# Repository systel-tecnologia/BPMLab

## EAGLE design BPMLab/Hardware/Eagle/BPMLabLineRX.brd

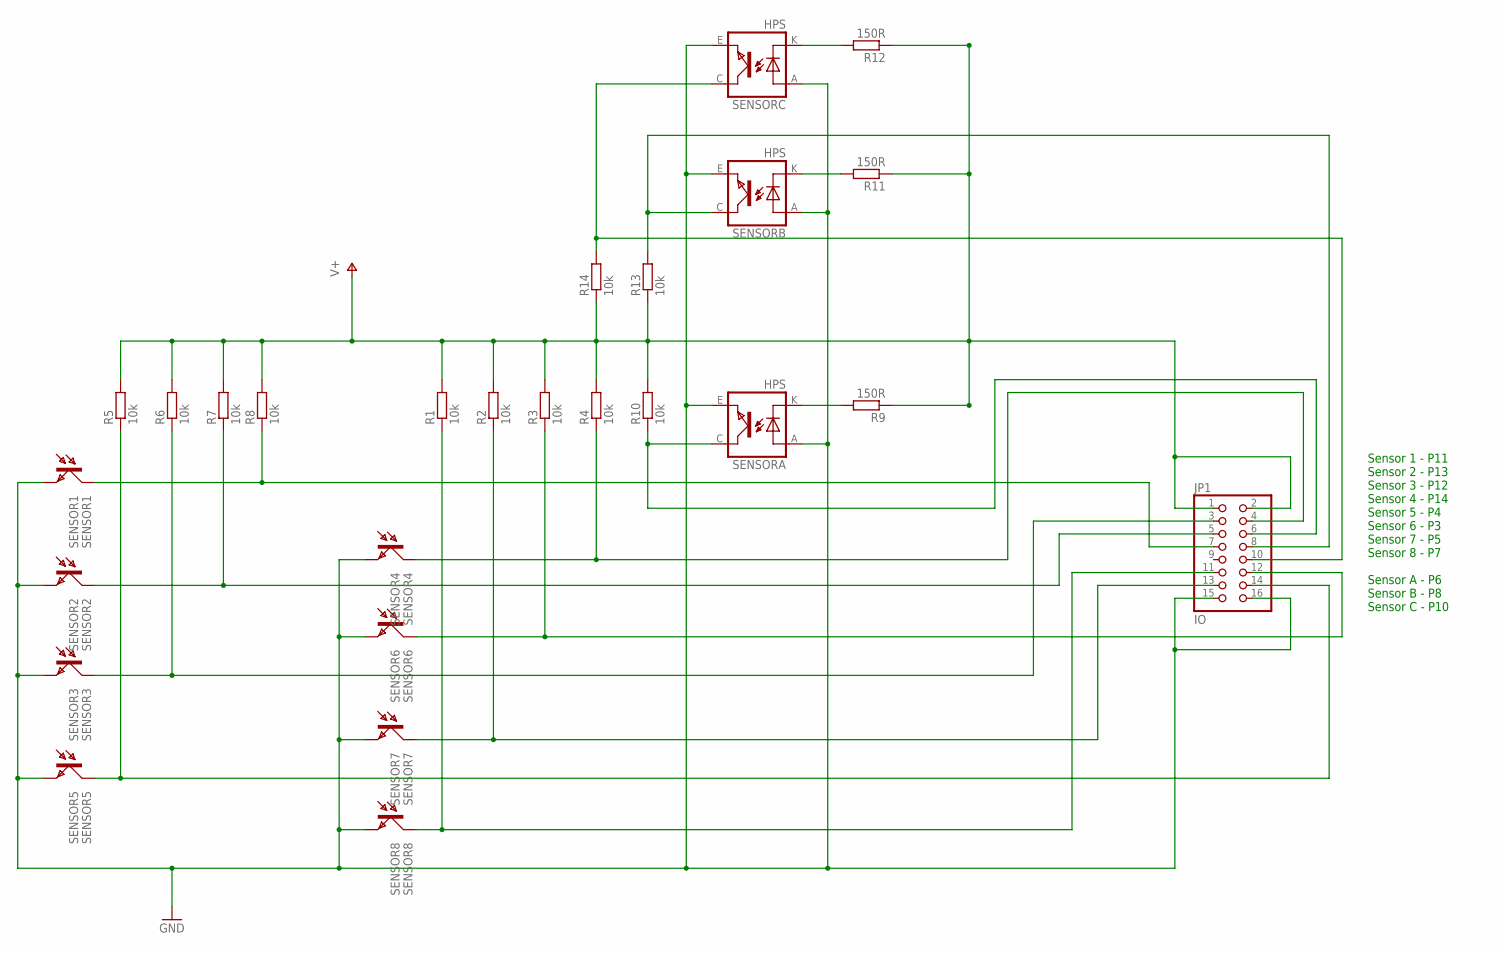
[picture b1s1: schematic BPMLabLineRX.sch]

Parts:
JP1: IO; 2X08
R1, R2, R3, R4, R5, R6, R7, R8, R10, R13, R14: 10k; M0805
R9, R11, R12: 150R; M0805
SENSOR1: SENSOR1; BPX81
SENSOR2: SENSOR2; BPX81
SENSOR3: SENSOR3; BPX81
SENSOR4: SENSOR4; BPX81
SENSOR5: SENSOR5; BPX81
SENSOR6: SENSOR6; BPX81
SENSOR7: SENSOR7; BPX81
SENSOR8: SENSOR8; BPX81
SENSORA: HPS; TCRT5000
SENSORB: HPS; TCRT5000
SENSORC: HPS; TCRT5000

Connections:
GND: JP1.15, JP1.16, SENSOR1.E, SENSOR2.E, SENSOR3.E, SENSOR4.E, SENSOR5.E, SENSOR6.E, SENSOR7.E, SENSOR8.E, SENSORA.A (ANODE), SENSORA.E (EMITTER), SENSORB.A (ANODE), SENSORB.E (EMITTER), SENSORC.A (ANODE), SENSORC.E (EMITTER)
unnamed: JP1.4, R4.1, SENSOR4.C
unnamed: JP1.12, R3.1, SENSOR6.C
unnamed: JP1.13, R2.1, SENSOR7.C
unnamed: JP1.11, R1.1, SENSOR8.C
unnamed: JP1.7, R8.1, SENSOR1.C
unnamed: JP1.5, R7.1, SENSOR2.C
unnamed: JP1.3, R6.1, SENSOR3.C
unnamed: JP1.14, R5.1, SENSOR5.C
unnamed: JP1.6, R10.1, SENSORA.C (COLLECTOR)
unnamed: R9.2, SENSORA.K (CATHODE)
unnamed: R12.2, SENSORC.K (CATHODE)
unnamed: R11.2, SENSORB.K (CATHODE)
unnamed: JP1.8, R13.2, SENSORB.C (COLLECTOR)
unnamed: JP1.10, R14.2, SENSORC.C (COLLECTOR)
V+: JP1.1, JP1.2, R1.2, R2.2, R3.2, R4.2, R5.2, R6.2, R7.2, R8.2, R9.1, R10.2, R11.1, R12.1, R13.1, R14.1

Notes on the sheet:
Sensor 1 - P11 Sensor 2 - P13 Sensor 3 - P12 Sensor 4 - P14 Sensor 5 - P4 Sensor 6 - P3 Sensor 7 - P5 Sensor 8 - P7 Sensor A - P6 Sensor B - P8 Sensor C - P10

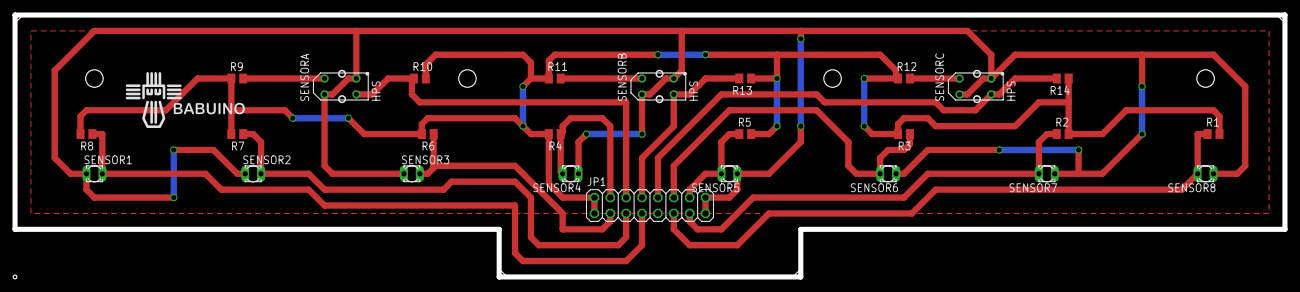
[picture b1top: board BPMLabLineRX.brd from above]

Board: 2 copper layers, 203.2 x 41.9 mm, 26 parts (0 on the bottom side), 16 nets.

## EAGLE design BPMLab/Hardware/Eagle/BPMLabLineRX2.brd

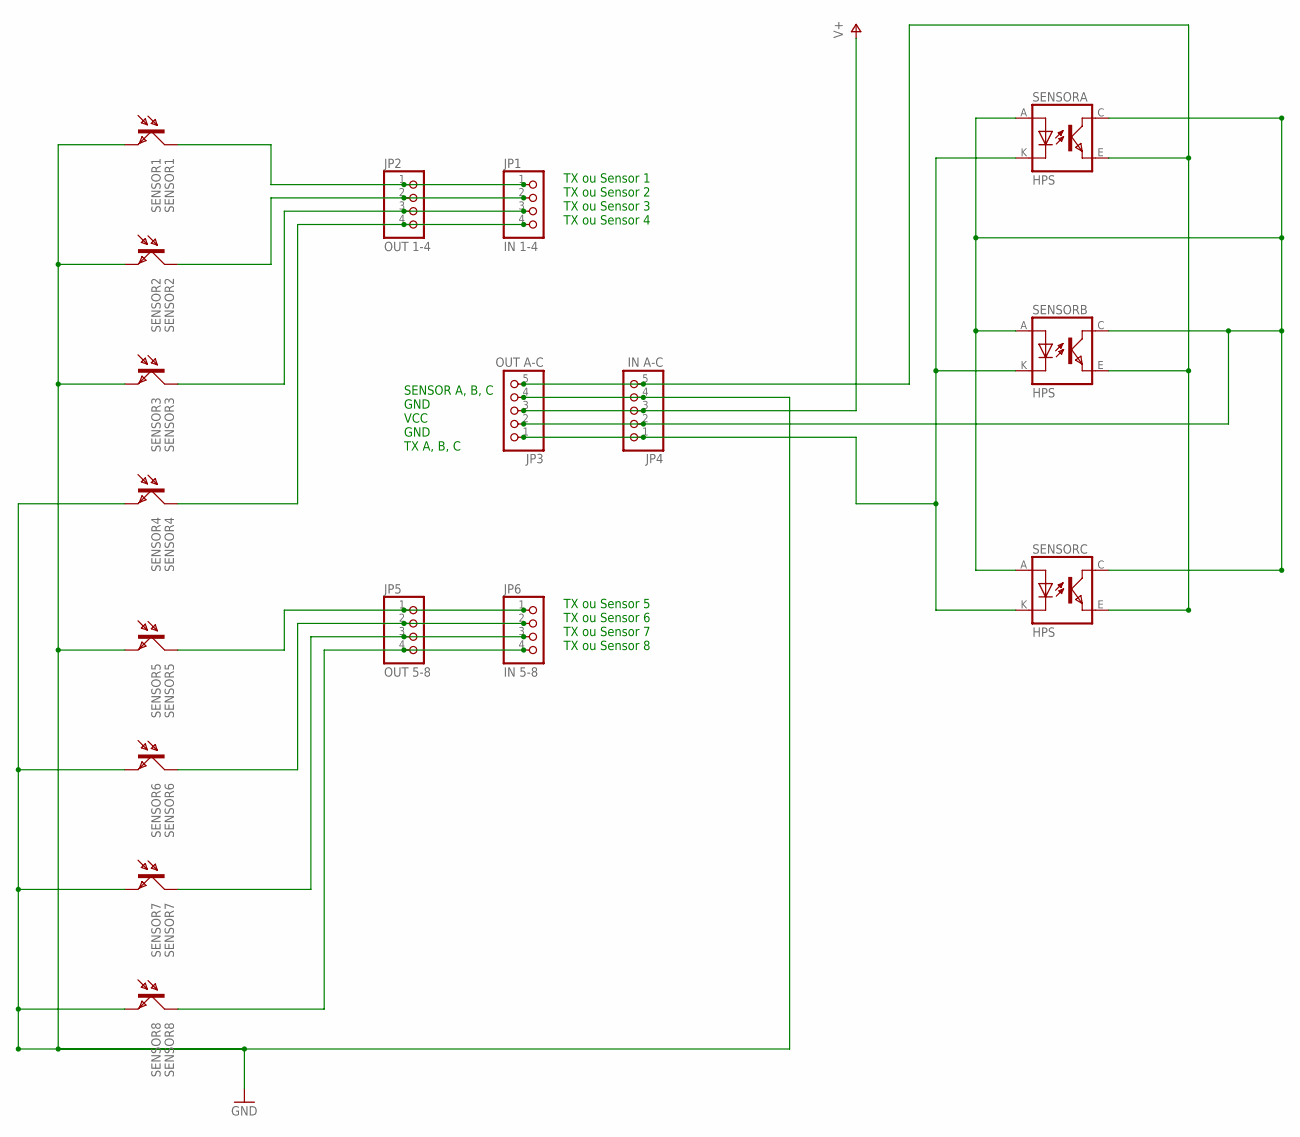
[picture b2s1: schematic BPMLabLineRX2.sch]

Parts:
JP1: IN 1-4; 1X04
JP2: OUT 1-4; 1X04
JP3: OUT A-C; 1X05
JP4: IN A-C; 1X05
JP5: OUT 5-8; 1X04
JP6: IN 5-8; 1X04
SENSOR1: SENSOR1; BPX81
SENSOR2: SENSOR2; BPX81
SENSOR3: SENSOR3; BPX81
SENSOR4: SENSOR4; BPX81
SENSOR5: SENSOR5; BPX81
SENSOR6: SENSOR6; BPX81
SENSOR7: SENSOR7; BPX81
SENSOR8: SENSOR8; BPX81
SENSORA: HPS; TCRT5000
SENSORB: HPS; TCRT5000
SENSORC: HPS; TCRT5000

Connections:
GND: JP3.4, JP4.4, SENSOR1.E, SENSOR2.E, SENSOR3.E, SENSOR4.E, SENSOR5.E, SENSOR6.E, SENSOR7.E, SENSOR8.E
unnamed: JP1.4, JP2.4, SENSOR4.C
unnamed: JP5.2, JP6.2, SENSOR6.C
unnamed: JP5.3, JP6.3, SENSOR7.C
unnamed: JP5.4, JP6.4, SENSOR8.C
unnamed: JP1.1, JP2.1, SENSOR1.C
unnamed: JP1.2, JP2.2, SENSOR2.C
unnamed: JP1.3, JP2.3, SENSOR3.C
unnamed: JP5.1, JP6.1, SENSOR5.C
unnamed: JP3.5, JP4.5, SENSORA.E (EMITTER), SENSORB.E (EMITTER), SENSORC.E (EMITTER)
unnamed: JP3.1, JP4.1, SENSORA.K (CATHODE), SENSORB.K (CATHODE), SENSORC.K (CATHODE)
unnamed: JP3.2, JP4.2, SENSORA.A (ANODE), SENSORA.C (COLLECTOR), SENSORB.A (ANODE), SENSORB.C (COLLECTOR), SENSORC.A (ANODE), SENSORC.C (COLLECTOR)
V+: JP3.3, JP4.3

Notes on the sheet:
TX ou Sensor 1 TX ou Sensor 2 TX ou Sensor 3 TX ou Sensor 4
TX ou Sensor 5 TX ou Sensor 6 TX ou Sensor 7 TX ou Sensor 8
SENSOR A, B, C GND VCC GND TX A, B, C

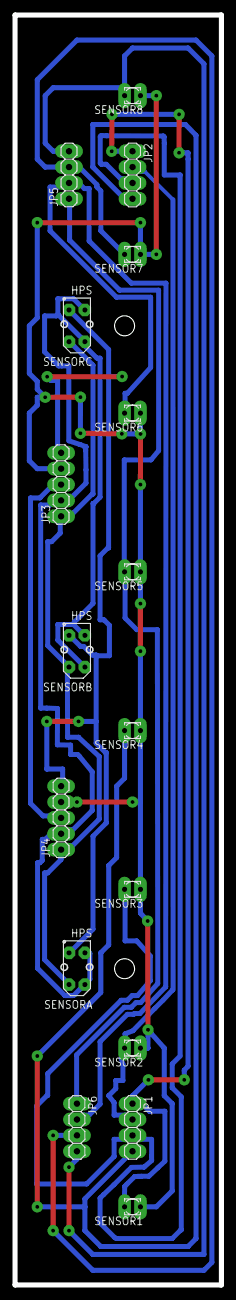
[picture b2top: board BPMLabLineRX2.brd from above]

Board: 2 copper layers, 33.0 x 203.2 mm, 17 parts (0 on the bottom side), 13 nets.

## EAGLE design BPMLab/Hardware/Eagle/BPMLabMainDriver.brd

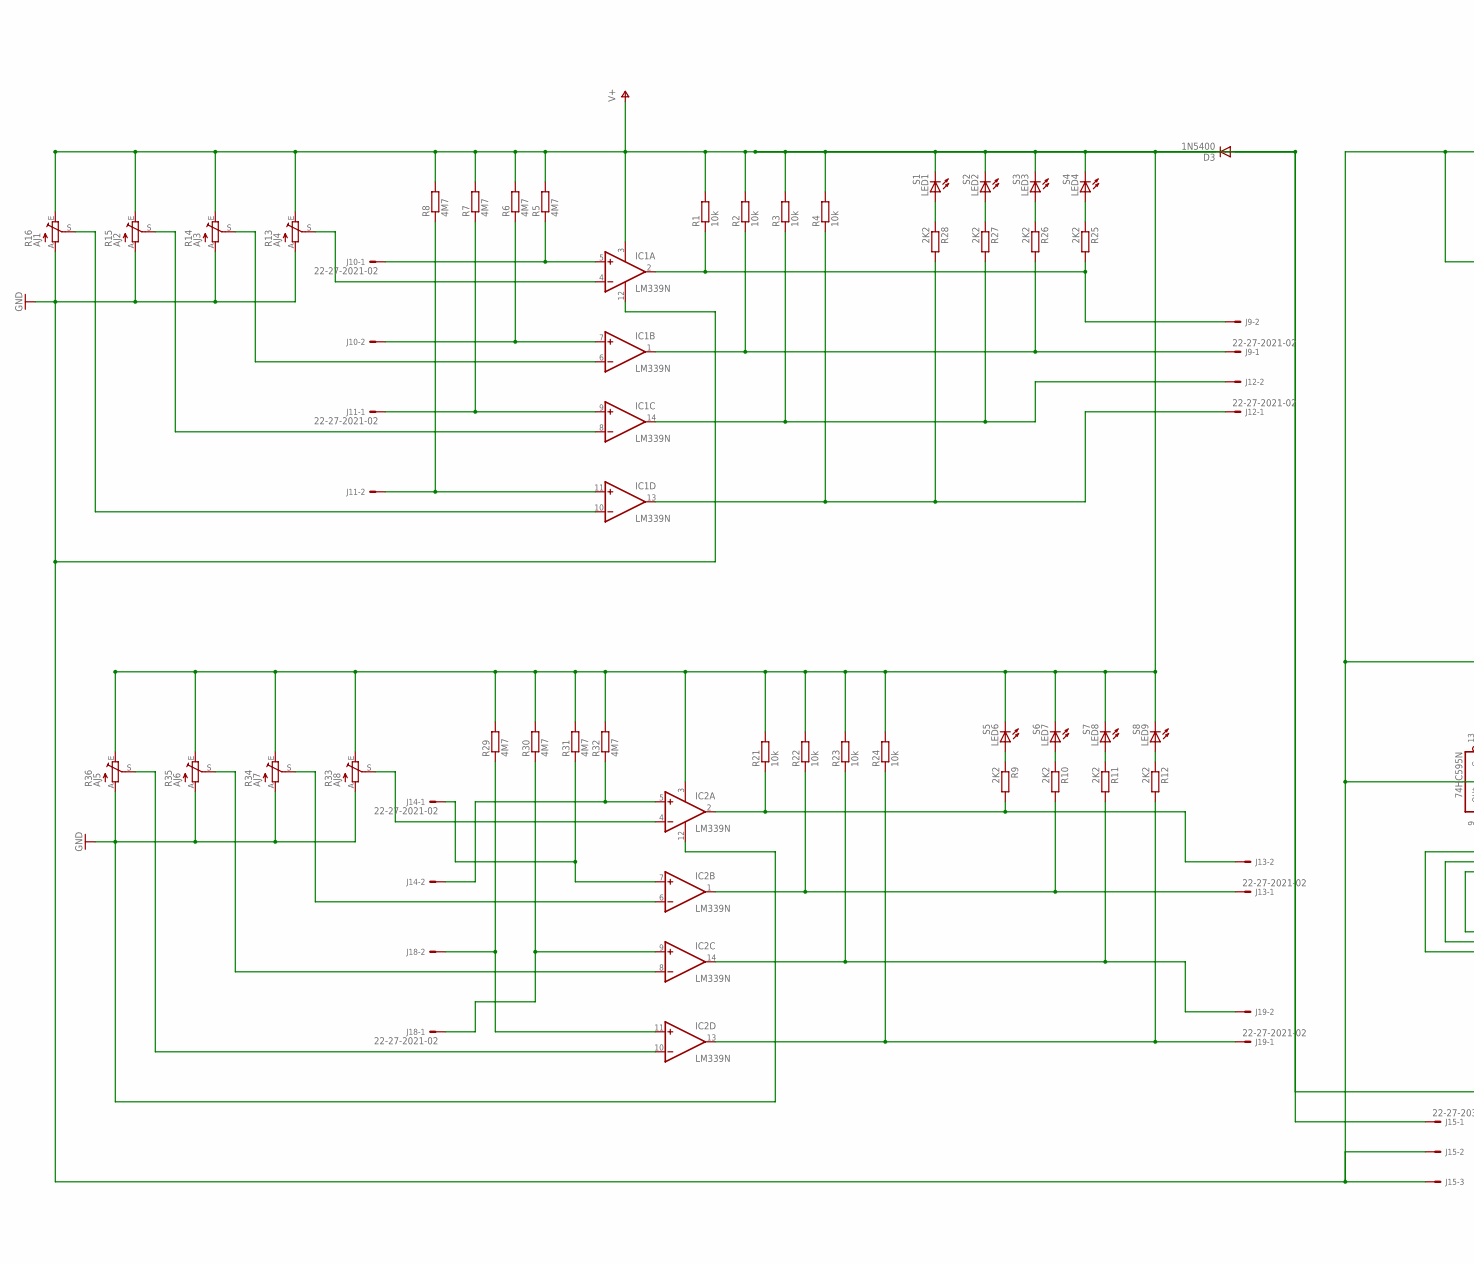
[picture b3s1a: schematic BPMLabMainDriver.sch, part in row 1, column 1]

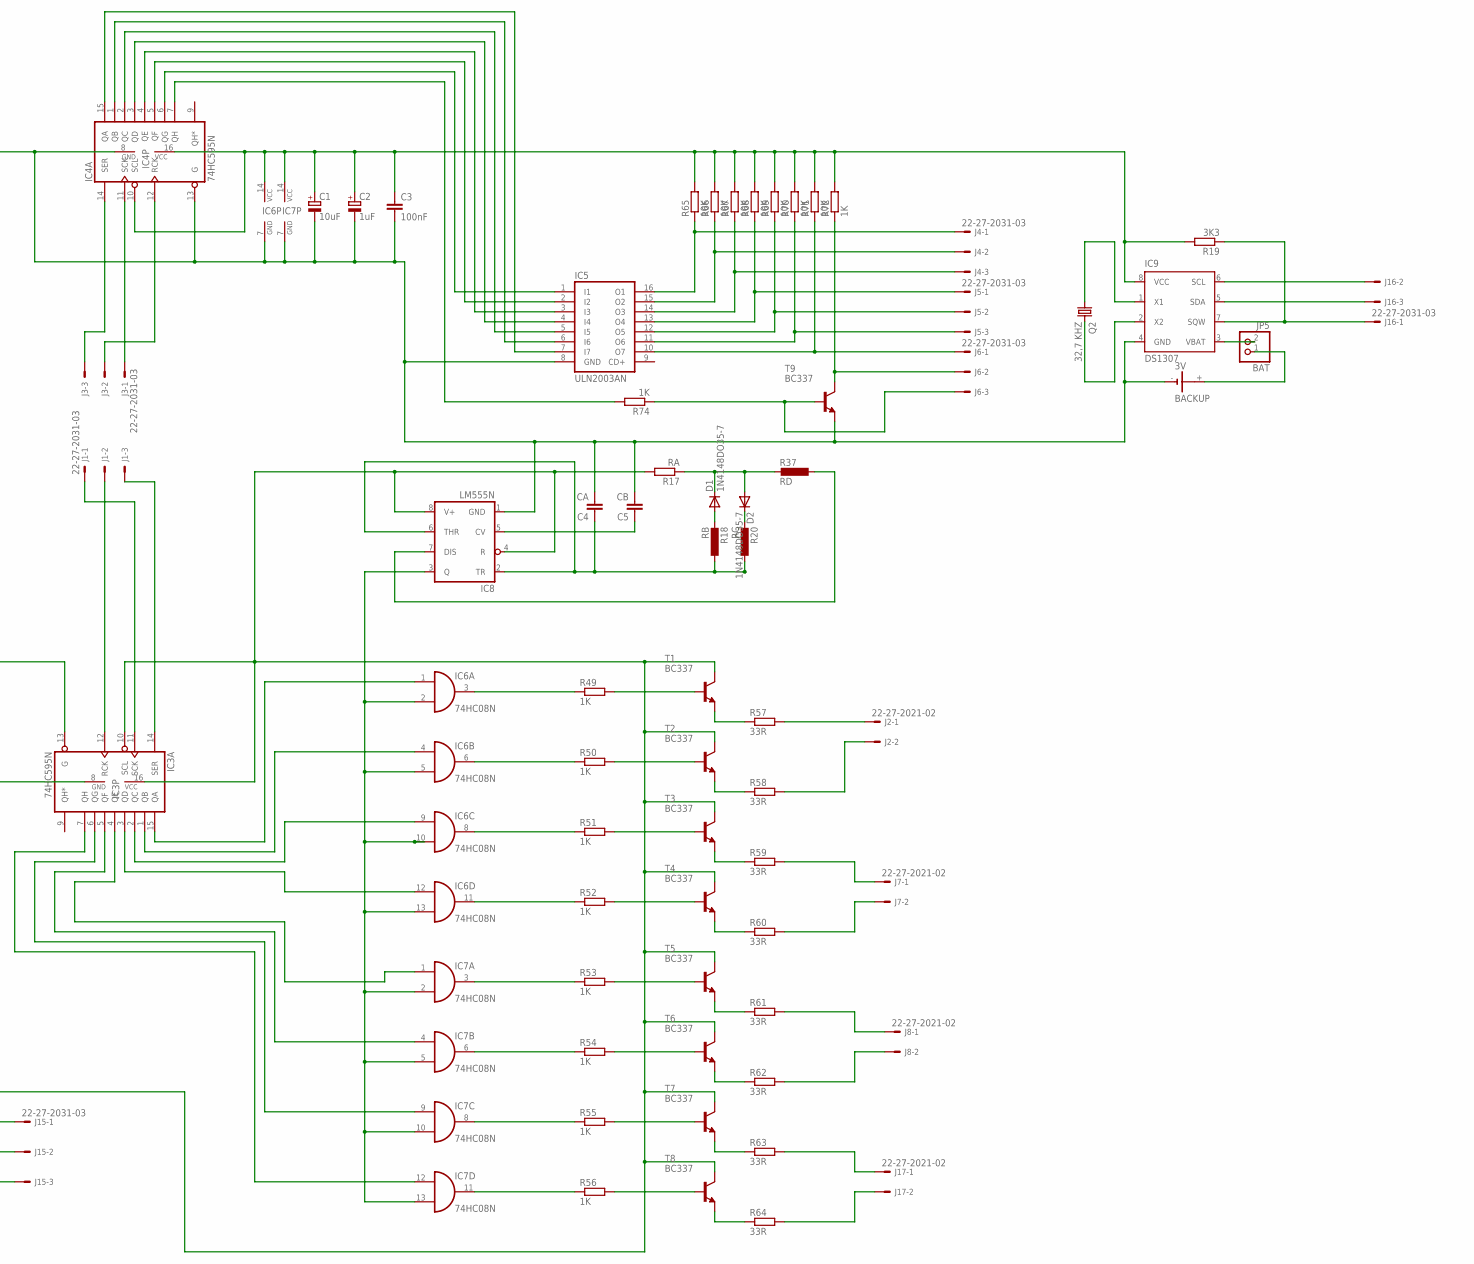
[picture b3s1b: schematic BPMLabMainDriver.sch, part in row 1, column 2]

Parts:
3V: BACKUP; CR2032V
BAT: JP5; 1X02
C1: 10uF; E2,5-6
C2: 1uF; E2,5-6
C3: 100nF; C050-024X044
C4: CA; C050-025X075
C5: CB; C050-024X044
D1, D2: 1N4148DO35-7; DO35-7
D3: 1N5400; DO201-15
IC1, IC2: LM339N; DIL14
IC3, IC4: 74HC595N; DIL16
IC5: ULN2003AN; DIL16
IC6, IC7: 74HC08N; DIL14
IC8: LM555N; DIL08
IC9: DS1307; DIL08
J1, J3, J4, J5, J6, J15, J16: 22-27-2031-03; 6410-03
J2, J7, J8, J9, J10, J11, J12, J13, J14, J17, J18, J19: 22-27-2021-02; 6410-02
LED1: S1; LED5MM
LED2: S2; LED5MM
LED3: S3; LED5MM
LED4: S4; LED5MM
LED6: S5; LED5MM
LED7: S6; LED5MM
LED8: S7; LED5MM
LED9: S8; LED5MM
Q2: 32,7 KHZ; TC38H
R1, R2, R3, R4, R21, R22, R23, R24: 10k; 0207/7
R5, R6, R7, R8, R30, R31, R32: 4M7; 0207/10
R9, R10, R11, R12, R25, R26, R27, R28: 2K2; 0207/7
R13: AJ4; RS3
R14: AJ3; RS3
R15: AJ2; RS3
R16: AJ1; RS3
R17: RA; 0207/10
R18: RB; 0207/12
R19: 3K3; 0207/10
R20: RC; 0207/12
R29: 4M7; 0207/7
R33: AJ8; RS3
R34: AJ7; RS3
R35: AJ6; RS3
R36: AJ5; RS3
R37: RD; 0207/12
R49, R50, R51, R52, R53, R54, R55, R72, R74: 1K; 0207/10
R56: 1K; 0207/12
R57, R58, R59, R60, R61, R62, R63, R64: 33R; 0207/10
R65, R66, R67, R68, R69, R70, R71: 10K; 0207/10
T1, T2, T3, T4, T5, T6, T7, T8, T9: BC337; TO92

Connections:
GND: 3V.-, C1.-, C2.-, C3.2, C4.2, C5.2, IC1.12 (GND), IC2.12 (GND), IC3.8 (GND), IC3.13 (G), IC4.8 (GND), IC4.13 (G), IC5.8 (GND), IC6.7 (GND), IC7.7 (GND), IC8.1 (GND), IC9.4 (GND), J15.2, J15.3, R13.A, R14.A, R15.A, R16.A, R33.A, R34.A, R35.A, R36.A, T9.1 (E)
unnamed: IC1.2 (OUT), J9.2, R1.1, R25.2
unnamed: IC1.1 (OUT), J9.1, R2.1, R26.2
unnamed: IC1.14 (OUT), J12.2, R3.1, R27.2
unnamed: IC1.13 (OUT), J12.1, R4.1, R28.2
unnamed: IC1.5 (+IN), J10.1, R5.1
unnamed: IC1.7 (+IN), J10.2, R6.1
unnamed: IC1.9 (+IN), J11.1, R7.1
unnamed: IC1.11 (+IN), J11.2, R8.1
unnamed: IC5.16 (O1), J4.1, R65.1
unnamed: IC1.10 (-IN), R16.S
unnamed: IC1.8 (-IN), R15.S
unnamed: IC1.4 (-IN), R13.S
unnamed: IC1.6 (-IN), R14.S
unnamed: IC6.2 (I1), IC6.5 (I1), IC6.10 (I1), IC6.13 (I1), IC7.2 (I1), IC7.5 (I1), IC7.10 (I1), IC7.13 (I1), IC8.3 (Q)
unnamed: D1.A, R18.2
unnamed: D2.C, R20.2
unnamed: LED6.A, R9.1
unnamed: LED7.A, R10.1
unnamed: LED8.A, R11.1
unnamed: LED9.A, R12.1
unnamed: IC3.1 (QB), IC6.4 (I0)
unnamed: D1.C, D2.A, R17.1, R37.2
unnamed: C5.1, IC8.5 (CV)
unnamed: IC8.7 (DIS), R37.1
unnamed: IC2.2 (OUT), J13.2, R9.2, R21.1
unnamed: 3V.+, BAT.1
unnamed: IC2.1 (OUT), J13.1, R10.2, R22.1
unnamed: LED1.A, R28.1
unnamed: LED2.A, R27.1
unnamed: LED3.A, R26.1
unnamed: LED4.A, R25.1
unnamed: IC2.14 (OUT), J19.2, R11.2, R23.1
unnamed: IC2.13 (OUT), J19.1, R12.2, R24.1
unnamed: IC2.10 (-IN), R36.S
unnamed: IC2.8 (-IN), R35.S
unnamed: IC2.4 (-IN), R33.S
unnamed: IC2.6 (-IN), R34.S
unnamed: IC2.5 (+IN), J14.2, R32.1
unnamed: IC2.7 (+IN), J14.1, R31.1
unnamed: IC2.9 (+IN), J18.1, R30.1
unnamed: IC2.11 (+IN), J18.2, R29.1
unnamed: IC9.6 (SCL), J16.2
unnamed: IC9.5 (SDA), J16.3
unnamed: IC3.2 (QC), IC6.9 (I0)
unnamed: IC3.3 (QD), IC6.12 (I0)
unnamed: IC3.4 (QE), IC7.1 (I0)
unnamed: IC3.5 (QF), IC7.4 (I0)
unnamed: IC3.6 (QG), IC7.9 (I0)
unnamed: IC3.7 (QH), IC7.12 (I0)
unnamed: IC6.3 (O), R49.1
unnamed: IC6.6 (O), R50.1
unnamed: IC6.8 (O), R51.1
unnamed: IC3.15 (QA), IC6.1 (I0)
unnamed: IC6.11 (O), R52.1
unnamed: IC7.3 (O), R53.1
unnamed: IC7.6 (O), R54.1
unnamed: IC7.8 (O), R55.1
unnamed: IC7.11 (O), R56.1
unnamed: C4.1, IC8.2 (TR), IC8.6 (THR), R18.1, R20.1
unnamed: J17.2, R64.2
unnamed: R49.2, T1.2 (B)
unnamed: R50.2, T2.2 (B)
unnamed: R51.2, T3.2 (B)
unnamed: R52.2, T4.2 (B)
unnamed: R53.2, T5.2 (B)
unnamed: R54.2, T6.2 (B)
unnamed: R56.2, T8.2 (B)
unnamed: R55.2, T7.2 (B)
unnamed: R57.1, T1.1 (E)
unnamed: R58.1, T2.1 (E)
unnamed: R59.1, T3.1 (E)
unnamed: R60.1, T4.1 (E)
unnamed: R61.1, T5.1 (E)
unnamed: R62.1, T6.1 (E)
unnamed: R63.1, T7.1 (E)
unnamed: R64.1, T8.1 (E)
unnamed: J8.1, R61.2
unnamed: IC3.11 (SCK), J1.1
unnamed: IC3.12 (RCK), J1.2
unnamed: IC3.14 (SER), J1.3
unnamed: J8.2, R62.2
unnamed: J17.1, R63.2
unnamed: J7.2, R60.2
unnamed: J7.1, R59.2
unnamed: J2.2, R58.2
unnamed: J2.1, R57.2
unnamed: IC4.15 (QA), IC5.7 (I7)
unnamed: IC4.1 (QB), IC5.6 (I6)
unnamed: IC4.2 (QC), IC5.5 (I5)
unnamed: IC4.3 (QD), IC5.4 (I4)
unnamed: IC4.4 (QE), IC5.3 (I3)
unnamed: IC4.5 (QF), IC5.2 (I2)
unnamed: IC4.6 (QG), IC5.1 (I1)
unnamed: IC5.15 (O2), J4.2, R66.1
unnamed: IC5.14 (O3), J4.3, R67.1
unnamed: IC4.11 (SCK), J3.1
unnamed: IC4.12 (RCK), J3.2
unnamed: IC4.14 (SER), J3.3
unnamed: IC5.13 (O4), J5.1, R68.1
unnamed: D3.A, J15.1
unnamed: IC5.12 (O5), J5.2, R69.1
unnamed: IC5.11 (O6), J5.3, R70.1
unnamed: IC5.10 (O7), J6.1, R71.1
unnamed: J6.2, R72.1, T9.3 (C)
unnamed: J6.3, R74.1, T9.2 (B)
unnamed: IC4.7 (QH), R74.2
unnamed: IC9.7 (SQW), J16.1, R19.1
unnamed: IC9.1 (X1), Q2.1
unnamed: IC9.2 (X2), Q2.2
unnamed: BAT.2, IC9.3 (VBAT)
VCC: C1.+, C2.+, C3.1, D3.C, IC1.3 (V+), IC2.3 (V+), IC3.10 (SCL), IC3.16 (VCC), IC4.10 (SCL), IC4.16 (VCC), IC6.14 (VCC), IC7.14 (VCC), IC8.4 (R), IC8.8 (V+), IC9.8 (VCC), LED1.K (C), LED2.K (C), LED3.K (C), LED4.K (C), LED6.K (C), LED7.K (C), LED8.K (C), LED9.K (C), R1.2, R2.2, R3.2, R4.2, R5.2, R6.2, R7.2, R8.2, R13.E, R14.E, R15.E, R16.E, R17.2, R19.2, R21.2, R22.2, R23.2, R24.2, R29.2, R30.2, R31.2, R32.2, R33.E, R34.E, R35.E, R36.E, R65.2, R66.2, R67.2, R68.2, R69.2, R70.2, R71.2, R72.2, T1.3 (C), T2.3 (C), T3.3 (C), T4.3 (C), T5.3 (C), T6.3 (C), T7.3 (C), T8.3 (C)

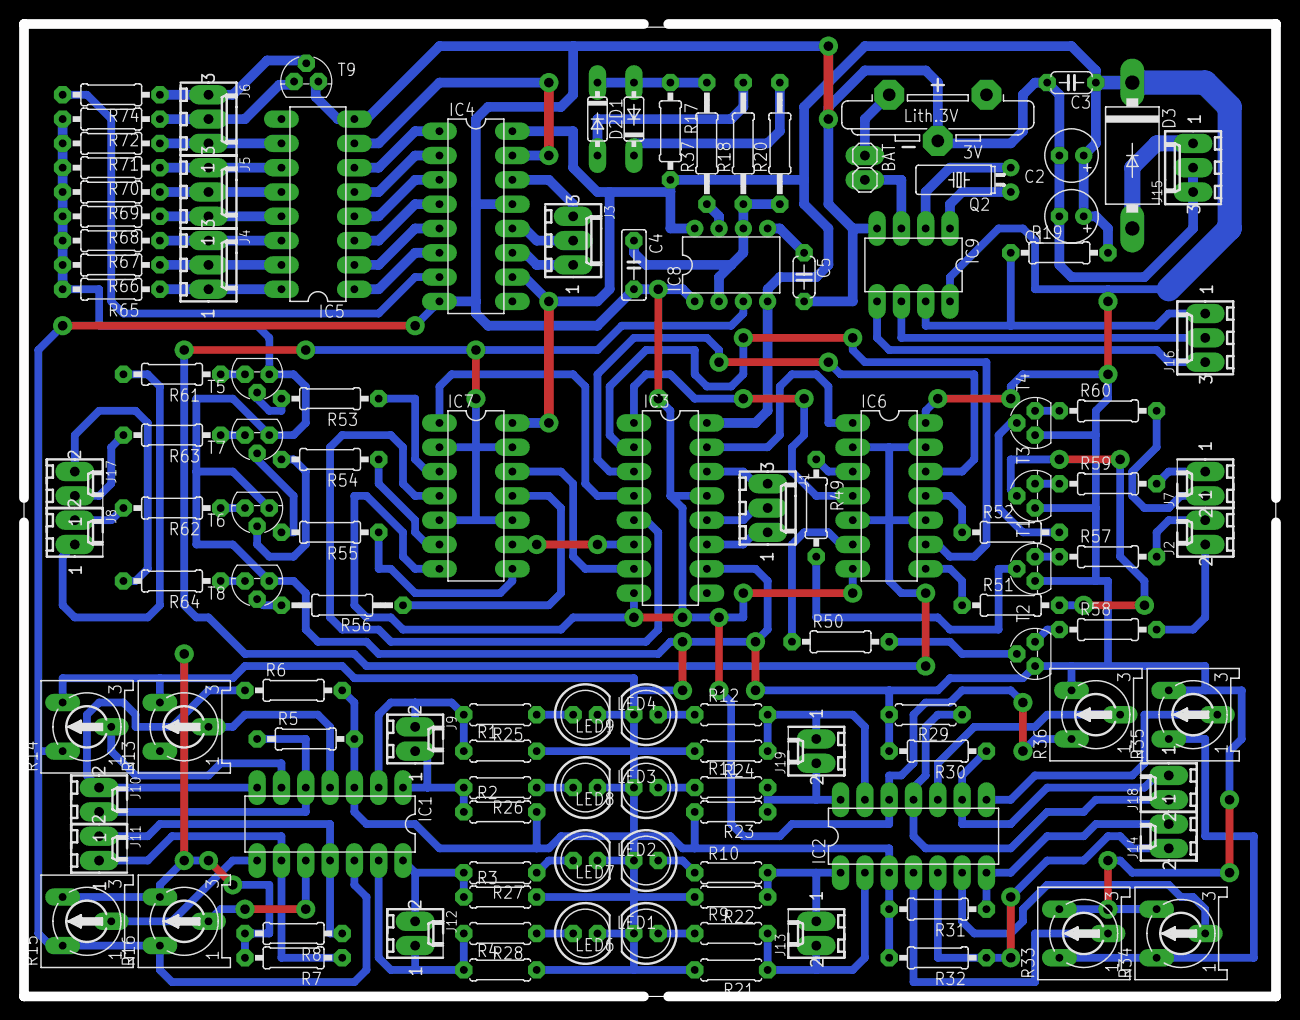
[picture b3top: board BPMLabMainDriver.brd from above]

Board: 2 copper layers, 130.8 x 101.6 mm, 118 parts (0 on the bottom side), 112 nets.

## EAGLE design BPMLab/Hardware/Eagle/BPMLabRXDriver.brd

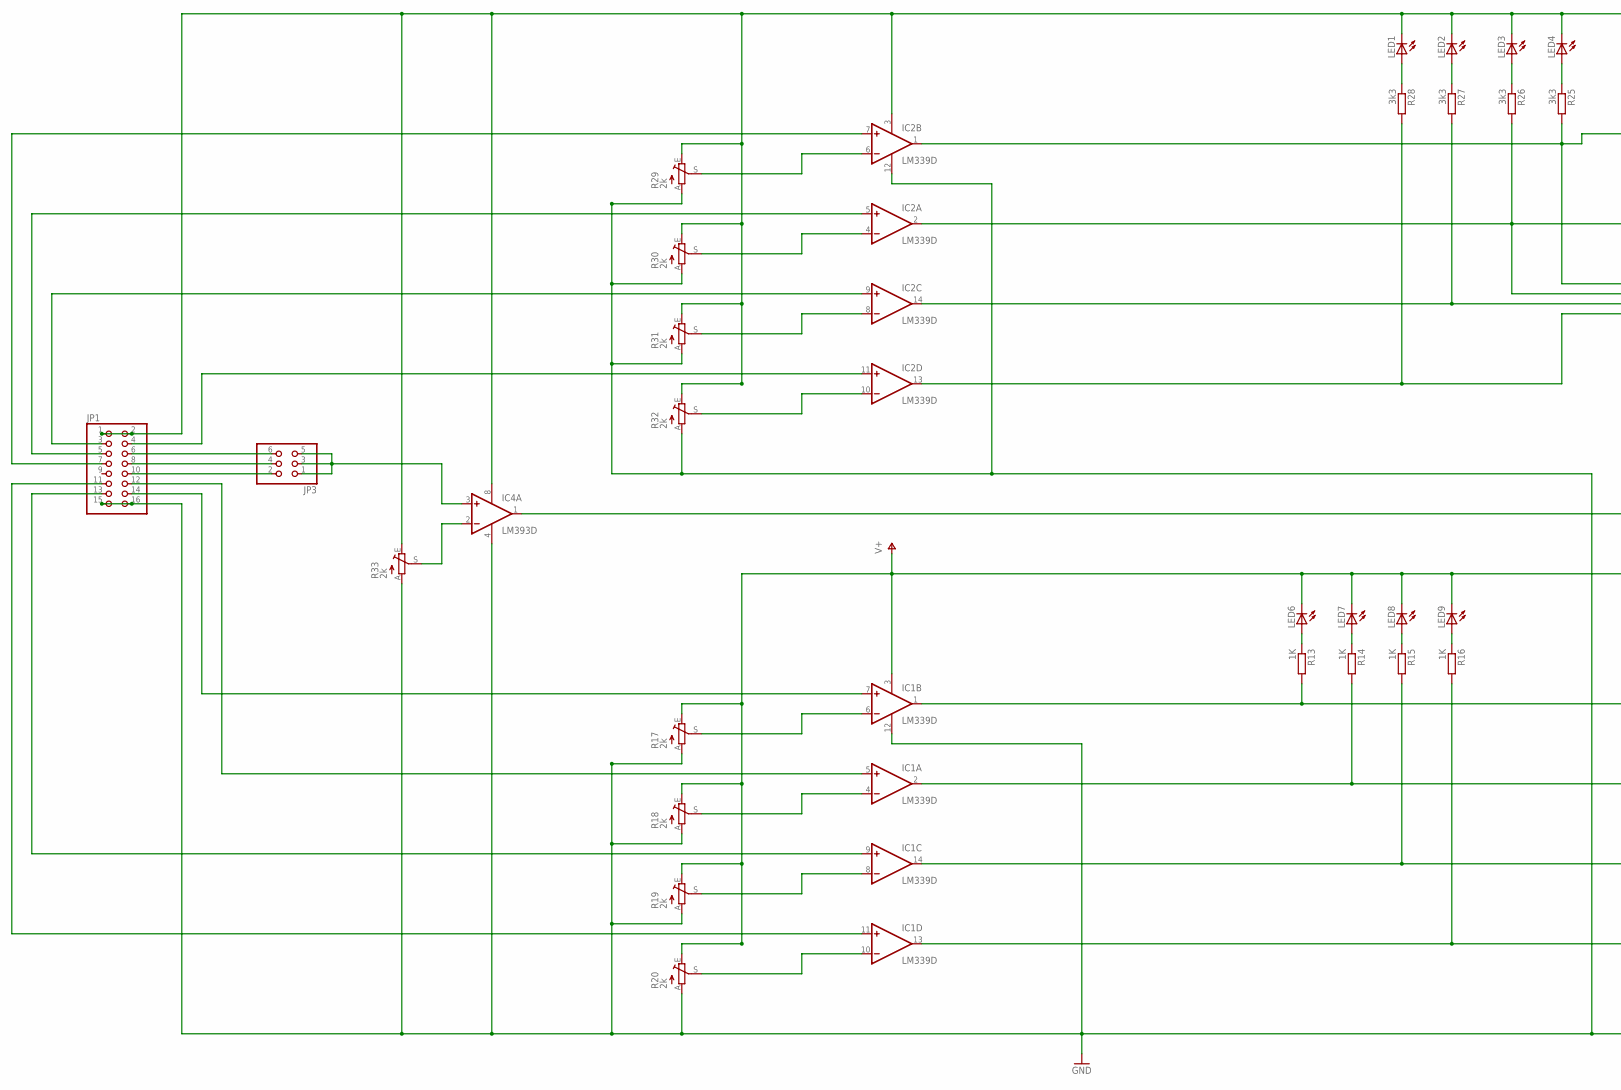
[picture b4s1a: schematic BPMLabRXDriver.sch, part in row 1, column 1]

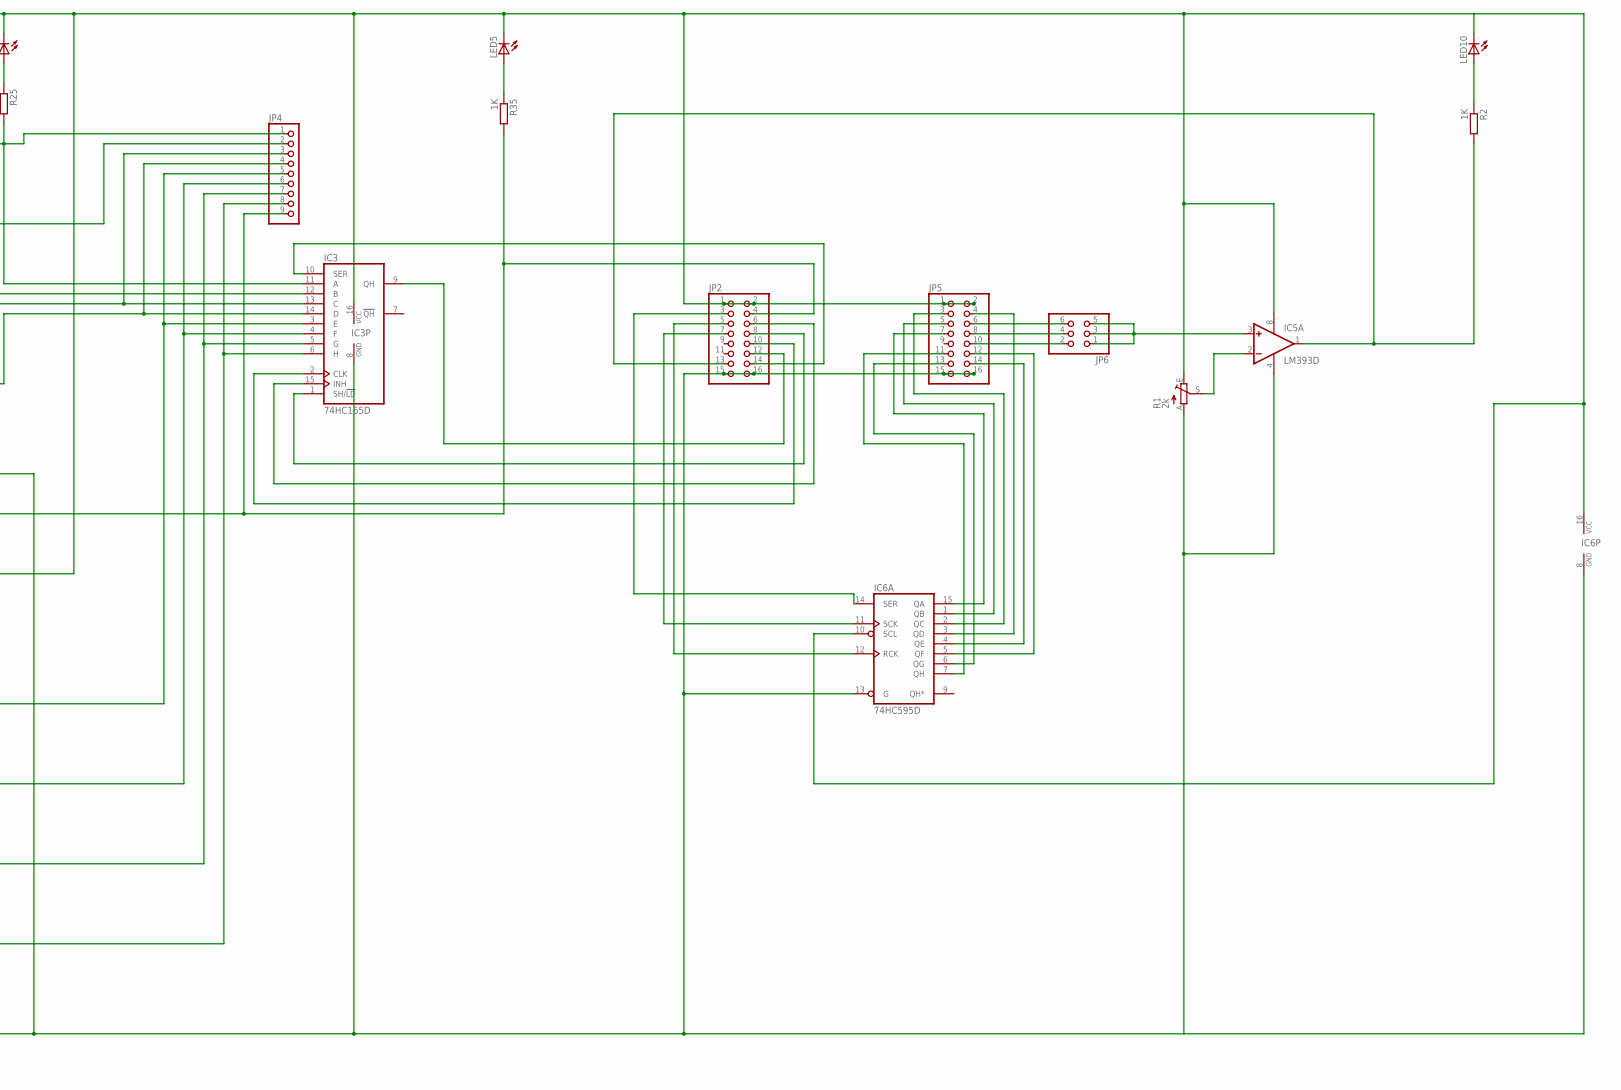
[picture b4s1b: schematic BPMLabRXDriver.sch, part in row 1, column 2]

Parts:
IC1, IC2: LM339D; SO14
IC3: 74HC165D; SO16
IC4, IC5: LM393D; SO08
IC6: 74HC595D; SO16
JP1, JP2, JP5: PINHD-2X8; 2X08
JP3, JP6: PINHD-2X3; 2X03
JP4: PINHD-1X9; 1X09
LED1, LED2, LED3, LED4, LED5, LED6, LED7, LED8, LED9, LED10: LED5MM
R1, R17, R18, R19, R20, R29, R30, R31, R32, R33: 2k; RS3
R2, R13, R14, R15, R16, R35: 1K; M0805
R25, R26, R27, R28: 3k3; M0805

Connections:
GND: IC1.12 (GND), IC2.12 (GND), IC3.8 (GND), IC4.4 (V-), IC5.4 (V-), IC6.8 (GND), IC6.13 (G), JP1.15, JP1.16, JP2.15, JP2.16, JP5.15, JP5.16, R1.A, R17.A, R18.A, R19.A, R20.A, R29.A, R30.A, R31.A, R32.A, R33.A
unnamed: IC1.7 (+IN), JP1.14
unnamed: IC3.10 (SER), JP2.14
unnamed: IC1.9 (+IN), JP1.13
unnamed: IC2.7 (+IN), JP1.7
unnamed: IC1.13 (OUT), IC3.6 (H), JP4.8, R16.2
unnamed: IC1.14 (OUT), IC3.5 (G), JP4.7, R15.2
unnamed: IC1.2 (OUT), IC3.4 (F), JP4.6, R14.2
unnamed: IC1.1 (OUT), IC3.3 (E), JP4.5, R13.2
unnamed: LED6.A, R13.1
unnamed: LED7.A, R14.1
unnamed: LED8.A, R15.1
unnamed: LED9.A, R16.1
unnamed: IC1.6 (-IN), R17.S
unnamed: JP5.6, JP6.6
unnamed: JP5.8, JP6.4
unnamed: JP5.10, JP6.2
unnamed: IC5.3 (+IN), JP6.1, JP6.3, JP6.5
unnamed: IC2.5 (+IN), JP1.5
unnamed: IC2.9 (+IN), JP1.3
unnamed: IC1.4 (-IN), R18.S
unnamed: IC1.8 (-IN), R19.S
unnamed: IC1.10 (-IN), R20.S
unnamed: IC2.13 (OUT), IC3.14 (D), JP4.4, R28.2
unnamed: IC2.14 (OUT), IC3.13 (C), JP4.3, R27.2
unnamed: IC1.11 (+IN), JP1.11
unnamed: IC2.2 (OUT), IC3.12 (B), JP4.2, R26.2
unnamed: IC2.1 (OUT), IC3.11 (A), JP4.1, R25.2
unnamed: LED1.A, R28.1
unnamed: LED2.A, R27.1
unnamed: LED3.A, R26.1
unnamed: LED4.A, R25.1
unnamed: LED5.A, R35.1
unnamed: IC6.15 (QA), JP5.7
unnamed: IC6.14 (SER), JP2.3
unnamed: IC5.2 (-IN), R1.S
unnamed: IC2.6 (-IN), R29.S
unnamed: IC2.4 (-IN), R30.S
unnamed: IC2.8 (-IN), R31.S
unnamed: IC2.10 (-IN), R32.S
unnamed: IC2.11 (+IN), JP1.4
unnamed: IC6.11 (SCK), JP2.7
unnamed: IC4.1 (OUT), JP2.4, JP4.9, R35.2
unnamed: IC3.15 (INH), JP2.6
unnamed: IC3.1 (SH/!LD), JP2.8
unnamed: IC3.2 (CLK), JP2.10
unnamed: IC3.9 (QH), JP2.12
unnamed: IC6.12 (RCK), JP2.5
unnamed: IC1.5 (+IN), JP1.12
unnamed: IC5.1 (OUT), JP2.13, R2.2
unnamed: JP1.6, JP3.6
unnamed: JP1.8, JP3.4
unnamed: JP1.10, JP3.2
unnamed: IC4.3 (+IN), JP3.1, JP3.3, JP3.5
unnamed: IC4.2 (-IN), R33.S
unnamed: IC6.1 (QB), JP5.5
unnamed: LED10.A, R2.1
unnamed: IC6.2 (QC), JP5.3
unnamed: IC6.3 (QD), JP5.4
unnamed: IC6.4 (QE), JP5.14
unnamed: IC6.5 (QF), JP5.12
unnamed: IC6.6 (QG), JP5.13
unnamed: IC6.7 (QH), JP5.11
VCC: IC1.3 (V+), IC2.3 (V+), IC3.16 (VCC), IC4.8 (V+), IC5.8 (V+), IC6.10 (SCL), IC6.16 (VCC), JP1.1, JP1.2, JP2.1, JP2.2, JP5.1, JP5.2, LED1.K (C), LED2.K (C), LED3.K (C), LED4.K (C), LED5.K (C), LED6.K (C), LED7.K (C), LED8.K (C), LED9.K (C), LED10.K (C), R1.E, R17.E, R18.E, R19.E, R20.E, R29.E, R30.E, R31.E, R32.E, R33.E

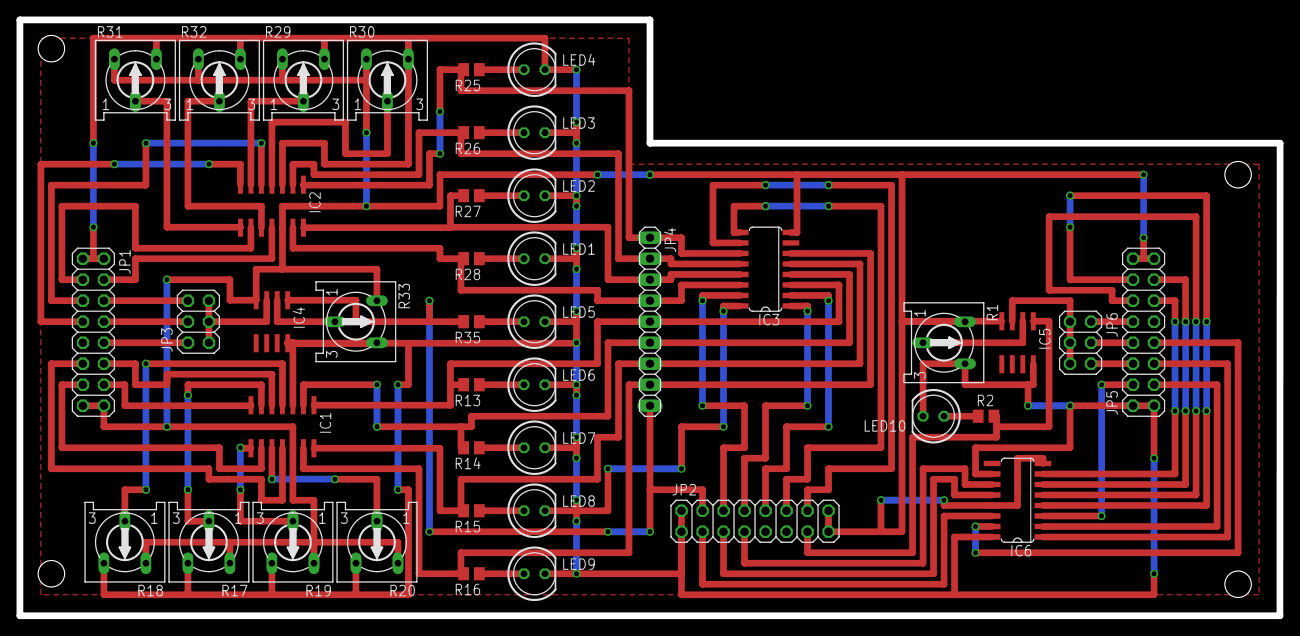
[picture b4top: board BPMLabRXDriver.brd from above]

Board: 2 copper layers, 152.4 x 72.1 mm, 42 parts (0 on the bottom side), 64 nets.

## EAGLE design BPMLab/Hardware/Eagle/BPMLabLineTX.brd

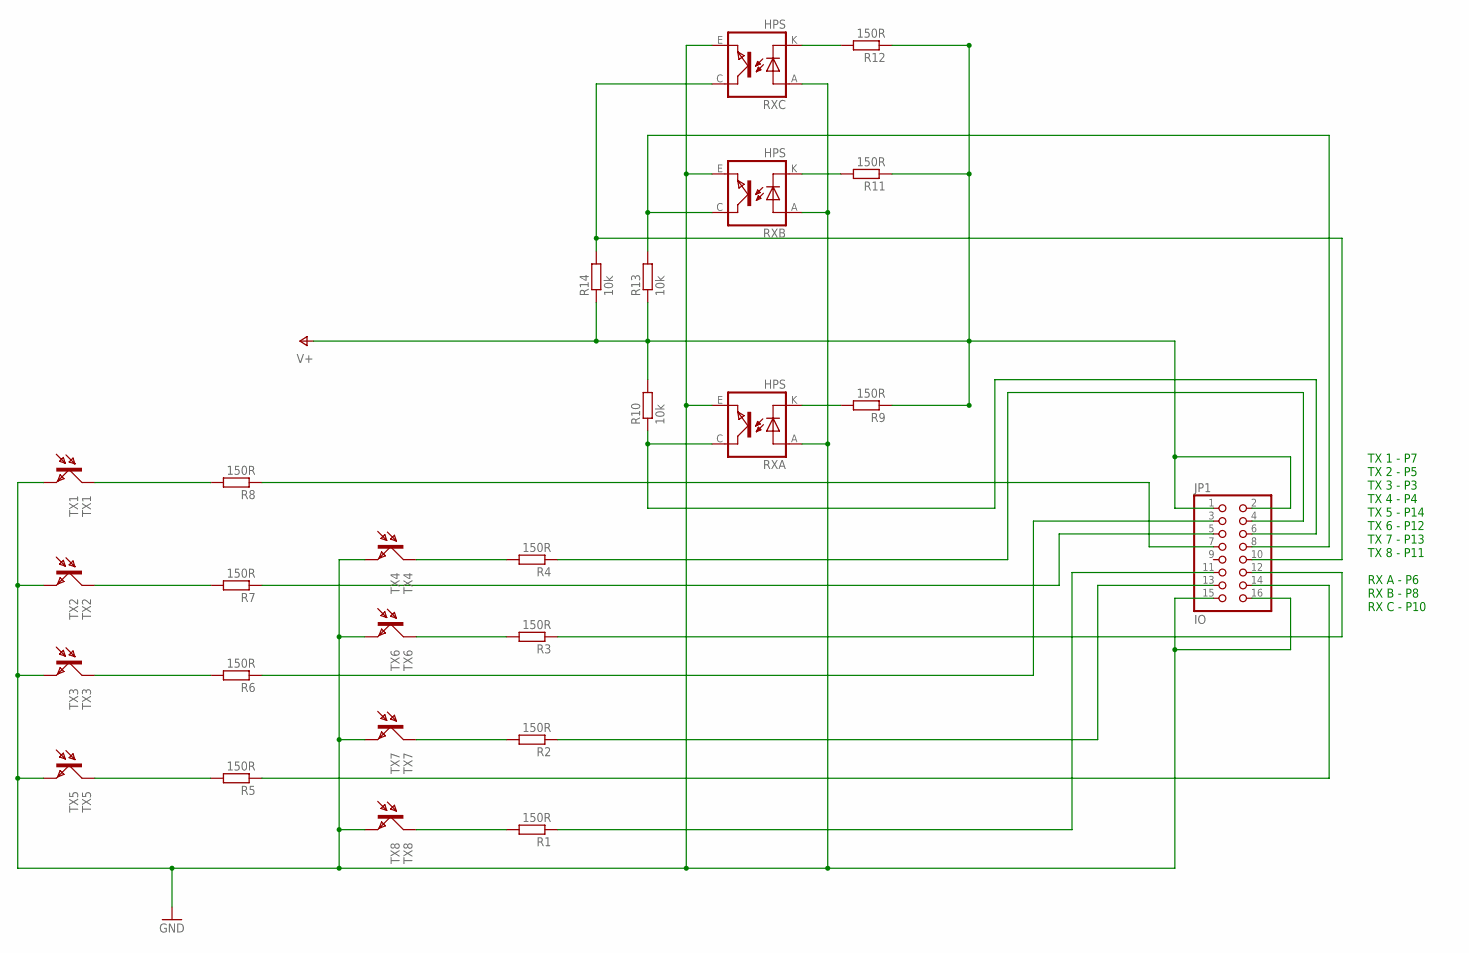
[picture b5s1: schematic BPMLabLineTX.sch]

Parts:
JP1: IO; 2X08
R1, R2, R3, R4, R5, R6, R7, R8, R9, R11, R12: 150R; M0805
R10, R13, R14: 10k; M0805
RXA: HPS; TCRT5000
RXB: HPS; TCRT5000
RXC: HPS; TCRT5000
TX1: TX1; BPX81
TX2: TX2; BPX81
TX3: TX3; BPX81
TX4: TX4; BPX81
TX5: TX5; BPX81
TX6: TX6; BPX81
TX7: TX7; BPX81
TX8: TX8; BPX81

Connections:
GND: JP1.15, JP1.16, RXA.A (ANODE), RXA.E (EMITTER), RXB.A (ANODE), RXB.E (EMITTER), RXC.A (ANODE), RXC.E (EMITTER), TX1.E, TX2.E, TX3.E, TX4.E, TX5.E, TX6.E, TX7.E, TX8.E
unnamed: JP1.4, R4.1
unnamed: JP1.12, R3.1
unnamed: JP1.13, R2.1
unnamed: JP1.11, R1.1
unnamed: JP1.7, R8.1
unnamed: JP1.5, R7.1
unnamed: JP1.3, R6.1
unnamed: JP1.14, R5.1
unnamed: JP1.6, R10.1, RXA.C (COLLECTOR)
unnamed: R9.2, RXA.K (CATHODE)
unnamed: R8.2, TX1.C
unnamed: R12.2, RXC.K (CATHODE)
unnamed: R11.2, RXB.K (CATHODE)
unnamed: R7.2, TX2.C
unnamed: R6.2, TX3.C
unnamed: JP1.8, R13.2, RXB.C (COLLECTOR)
unnamed: JP1.10, R14.2, RXC.C (COLLECTOR)
unnamed: R5.2, TX5.C
unnamed: R1.2, TX8.C
unnamed: R2.2, TX7.C
unnamed: R3.2, TX6.C
unnamed: R4.2, TX4.C
V+: JP1.1, JP1.2, R9.1, R10.2, R11.1, R12.1, R13.1, R14.1

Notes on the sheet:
TX 1 - P7 TX 2 - P5 TX 3 - P3 TX 4 - P4 TX 5 - P14 TX 6 - P12 TX 7 - P13 TX 8 - P11 RX A - P6 RX B - P8 RX C - P10

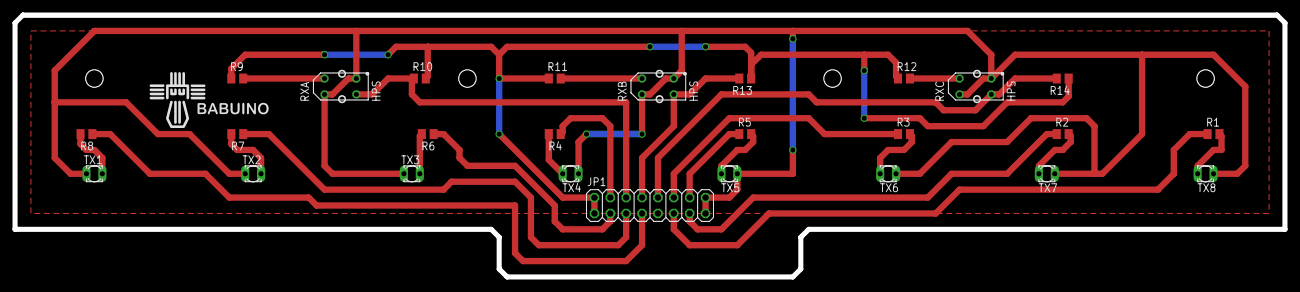
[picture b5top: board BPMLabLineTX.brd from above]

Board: 2 copper layers, 203.2 x 41.9 mm, 26 parts (0 on the bottom side), 24 nets.
